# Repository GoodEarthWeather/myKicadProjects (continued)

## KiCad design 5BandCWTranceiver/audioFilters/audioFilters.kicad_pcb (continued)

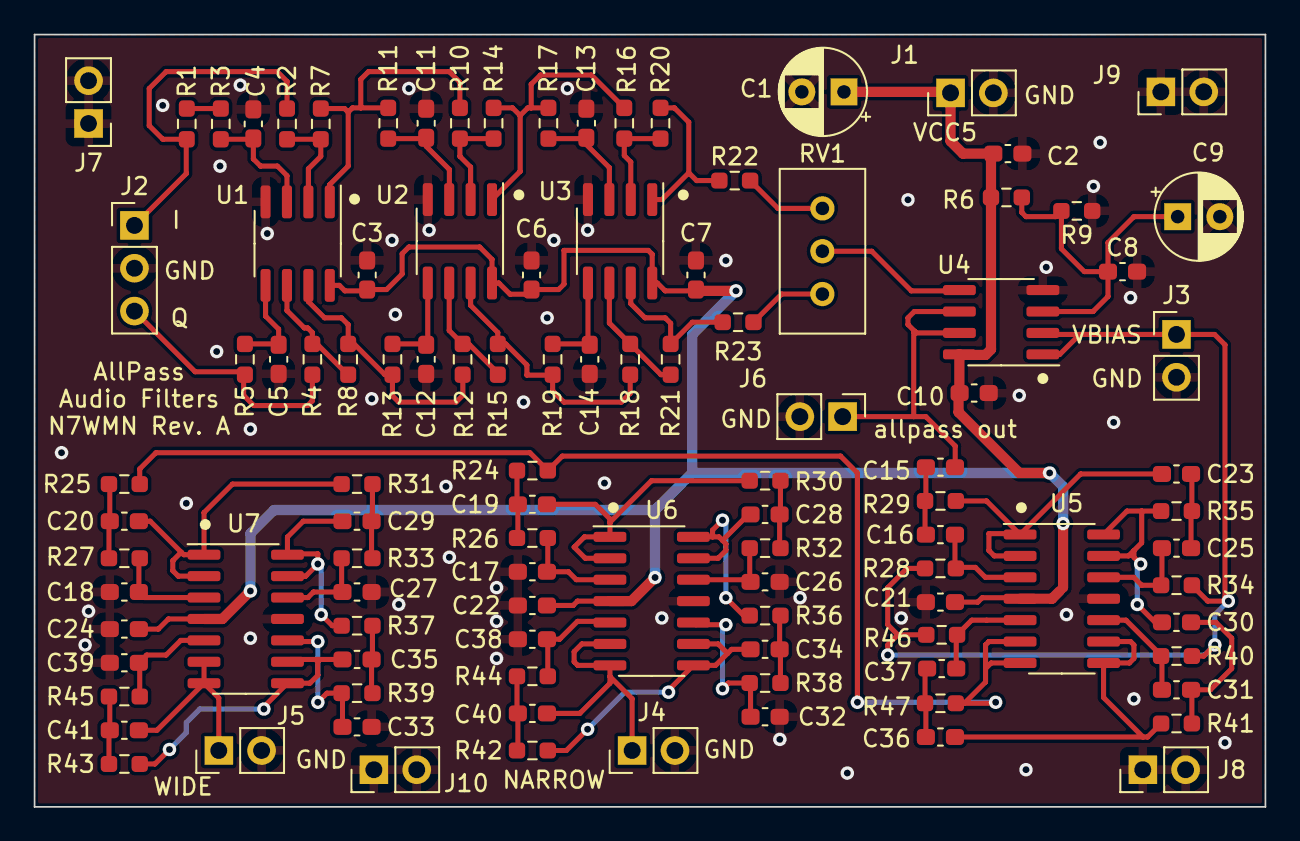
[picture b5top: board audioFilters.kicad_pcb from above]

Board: 2 copper layers, 73.0 x 45.8 mm, 106 parts (0 on the bottom side), 65 nets.

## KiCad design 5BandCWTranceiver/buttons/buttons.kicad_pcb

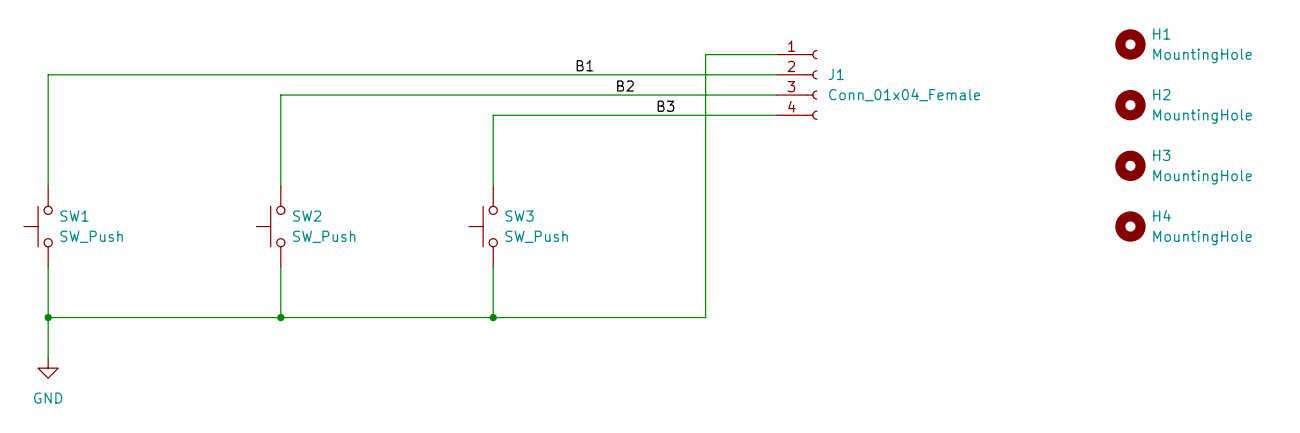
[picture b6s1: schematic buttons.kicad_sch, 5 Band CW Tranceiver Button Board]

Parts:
H1, H2, H3, H4: MountingHole; MountingHole_3.2mm_M3
J1: Conn_01x04_Female; PinHeader_1x04_P2.54mm_Vertical
SW1, SW2, SW3: SW_Push; SW_PUSH-12mm

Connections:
/B1: J1.2, SW1.2
/B2: J1.3, SW2.2
/B3: J1.4, SW3.2
GND: J1.1, SW1.1, SW2.1, SW3.1

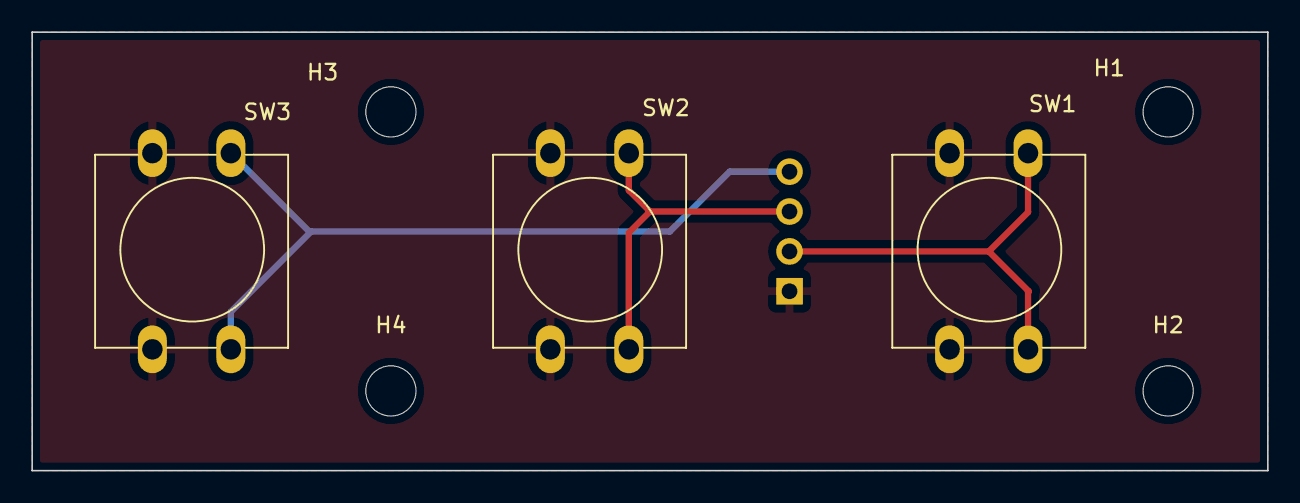
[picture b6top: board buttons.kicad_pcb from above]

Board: 2 copper layers, 78.7 x 27.9 mm, 8 parts (1 on the bottom side), 4 nets.

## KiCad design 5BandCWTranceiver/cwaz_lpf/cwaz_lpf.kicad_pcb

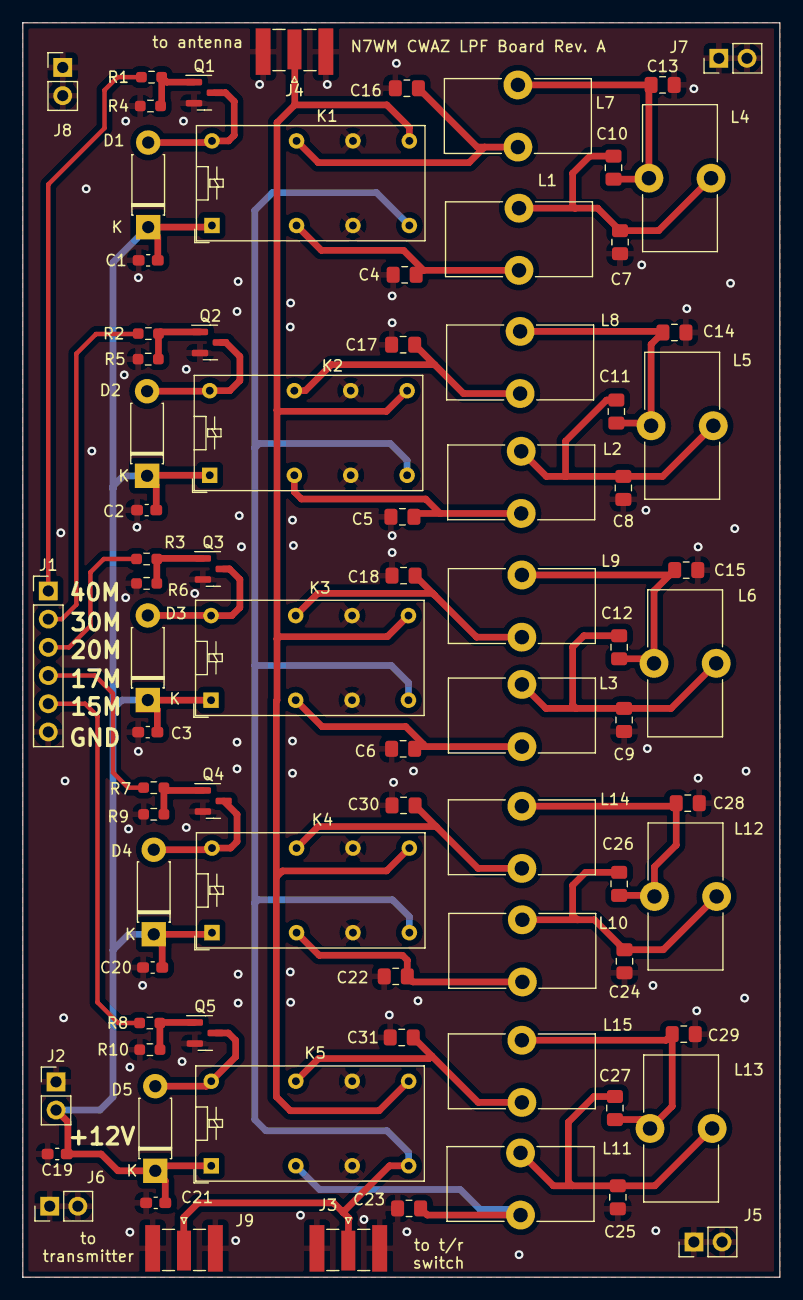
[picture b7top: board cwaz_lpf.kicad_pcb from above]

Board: 2 copper layers, 68.2 x 113.0 mm, 80 parts (0 on the bottom side), 39 nets.

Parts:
C1, C2, C3, C19, C20, C21: 0.1uF; C_0603_1608Metric_Pad1.08x0.95mm_HandSolder
C4, C16: 330p+100p; C_0805_2012Metric_Pad1.18x1.45mm_HandSolder
C5, C17: 150p+150p; C_0805_2012Metric_Pad1.18x1.45mm_HandSolder
C6, C18, C25, C29: 220p; C_0805_2012Metric_Pad1.18x1.45mm_HandSolder
C7, C13: 330p+330p; C_0805_2012Metric_Pad1.18x1.45mm_HandSolder
C8, C14: 470p; C_0805_2012Metric_Pad1.18x1.45mm_HandSolder
C9, C15: 330p; C_0805_2012Metric_Pad1.18x1.45mm_HandSolder
C10: 100p; C_0805_2012Metric_Pad1.18x1.45mm_HandSolder
C11: 68p; C_0805_2012Metric_Pad1.18x1.45mm_HandSolder
C12: 47p; C_0805_2012Metric_Pad1.18x1.45mm_HandSolder
C22, C30: 82p+82p; C_0805_2012Metric_Pad1.18x1.45mm_HandSolder
C23, C31: 150p; C_0805_2012Metric_Pad1.18x1.45mm_HandSolder
C24, C28: 100p+150p; C_0805_2012Metric_Pad1.18x1.45mm_HandSolder
C26: 39p; C_0805_2012Metric_Pad1.18x1.45mm_HandSolder
C27: 33p; C_0805_2012Metric_Pad1.18x1.45mm_HandSolder
D1, D2, D3, D4, D5: 1N4152; D_DO-41_SOD81_P7.62mm_Horizontal
J1: Conn_01x06_Male; PinHeader_1x06_P2.54mm_Vertical
J2, J5, J6, J7, J8: Conn_01x02_Male; PinHeader_1x02_P2.54mm_Vertical
J3, J4, J9: Conn_Coaxial; SMA_Samtec_SMA-J-P-X-ST-EM1_EdgeMount
K1, K2, K3, K4, K5: G5V-2; Relay_DPDT_Omron_G5V-2
L1, L7: 1.34uH; L_Toroid_Vertical_L13.0mm_W6.5mm_P5.60mm
L2, L8: 928nH; L_Toroid_Vertical_L13.0mm_W6.5mm_P5.60mm
L3, L9: 670nH; L_Toroid_Vertical_L13.0mm_W6.5mm_P5.60mm
L4: 1.22uH; L_Toroid_Vertical_L13.0mm_W6.5mm_P5.60mm
L5: 843nH; L_Toroid_Vertical_L13.0mm_W6.5mm_P5.60mm
L6: 608nH; L_Toroid_Vertical_L13.0mm_W6.5mm_P5.60mm
L10, L14: 519nH; L_Toroid_Vertical_L13.0mm_W6.5mm_P5.60mm
L11, L15: 447nH; L_Toroid_Vertical_L13.0mm_W6.5mm_P5.60mm
L12: 471nH; L_Toroid_Vertical_L13.0mm_W6.5mm_P5.60mm
L13: 406nH; L_Toroid_Vertical_L13.0mm_W6.5mm_P5.60mm
Q1, Q2, Q3, Q4, Q5: MMBT3904; SOT-23
R1, R2, R3, R4, R5, R6, R7, R8, R9, R10: R_US; R_0603_1608Metric_Pad0.98x0.95mm_HandSolder

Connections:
/15M: J1.5, R8.2
/17M: J1.4, R7.2
/20M: J1.3, R3.2
/30M: J1.2, R2.2
/40M: J1.1, R1.2
/VDD12: C1.1, C2.1, C3.1, C19.1, C20.1, C21.1, D1.1 (K), D2.1 (K), D3.1 (K), D4.1 (K), D5.1 (K), J2.2, K1.1, K2.1, K3.1, K4.1, K5.1
GND: C1.2, C2.2, C3.2, C4.2, C5.2, C6.2, C7.2, C8.2, C9.2, C13.2, C14.2, C15.2, C16.2, C17.2, C18.2, C19.2, C20.2, C21.2, C22.2, C23.2, C24.2, C25.2, C28.2, C29.2, C30.2, C31.2, J1.6, J2.1, J3.2 (Ext), J4.2 (Ext), J5.1, J5.2, J6.1, J6.2, J7.1, J7.2, J8.1, J8.2, J9.2 (Ext), K1.6, K1.11, K2.6, K2.11, K3.6, K3.11, K4.6, K4.11, K5.6, K5.11, Q1.2 (E), Q2.2 (E), Q3.2 (E), Q4.2 (E), Q5.2 (E), R4.2, R5.2, R6.2, R9.2, R10.2
unnamed: C5.1, K2.4, L2.2
unnamed: C6.1, K3.4, L3.2
unnamed: C10.1, C13.1, L4.1, L7.2
unnamed: C7.1, C10.2, L1.1, L4.2
unnamed: C11.1, C14.1, L5.1, L8.2
unnamed: C8.1, C11.2, L2.1, L5.2
unnamed: C12.1, C15.1, L6.1, L9.2
unnamed: C9.1, C12.2, L3.1, L6.2
unnamed: C16.1, K1.13, L7.1
unnamed: C17.1, K2.13, L8.1
unnamed: C18.1, K3.13, L9.1
unnamed: C23.1, K5.4, L11.2
unnamed: C24.1, C26.2, L10.1, L12.2
unnamed: C25.1, C27.2, L11.1, L13.2
unnamed: C26.1, C28.1, L12.1, L14.2
unnamed: C27.1, C29.1, L13.1, L15.2
unnamed: C30.1, K4.13, L14.1
unnamed: D1.2 (A), K1.16, Q1.3 (C)
unnamed: D2.2 (A), K2.16, Q2.3 (C)
unnamed: D3.2 (A), K3.16, Q3.3 (C)
unnamed: D4.2 (A), K4.16, Q4.3 (C)
unnamed: D5.2 (A), K5.16, Q5.3 (C)
unnamed: C4.1, K1.4, L1.2
unnamed: J3.1 (In), J9.1 (In), K1.8, K2.8, K3.8, K4.8, K5.8
unnamed: J4.1 (In), K1.9, K2.9, K3.9, K4.9, K5.9
unnamed: C22.1, K4.4, L10.2
unnamed: C31.1, K5.13, L15.1
unnamed: Q1.1 (B), R1.1, R4.1
unnamed: Q2.1 (B), R2.1, R5.1
unnamed: Q3.1 (B), R3.1, R6.1
unnamed: Q4.1 (B), R7.1, R9.1
unnamed: Q5.1 (B), R8.1, R10.1

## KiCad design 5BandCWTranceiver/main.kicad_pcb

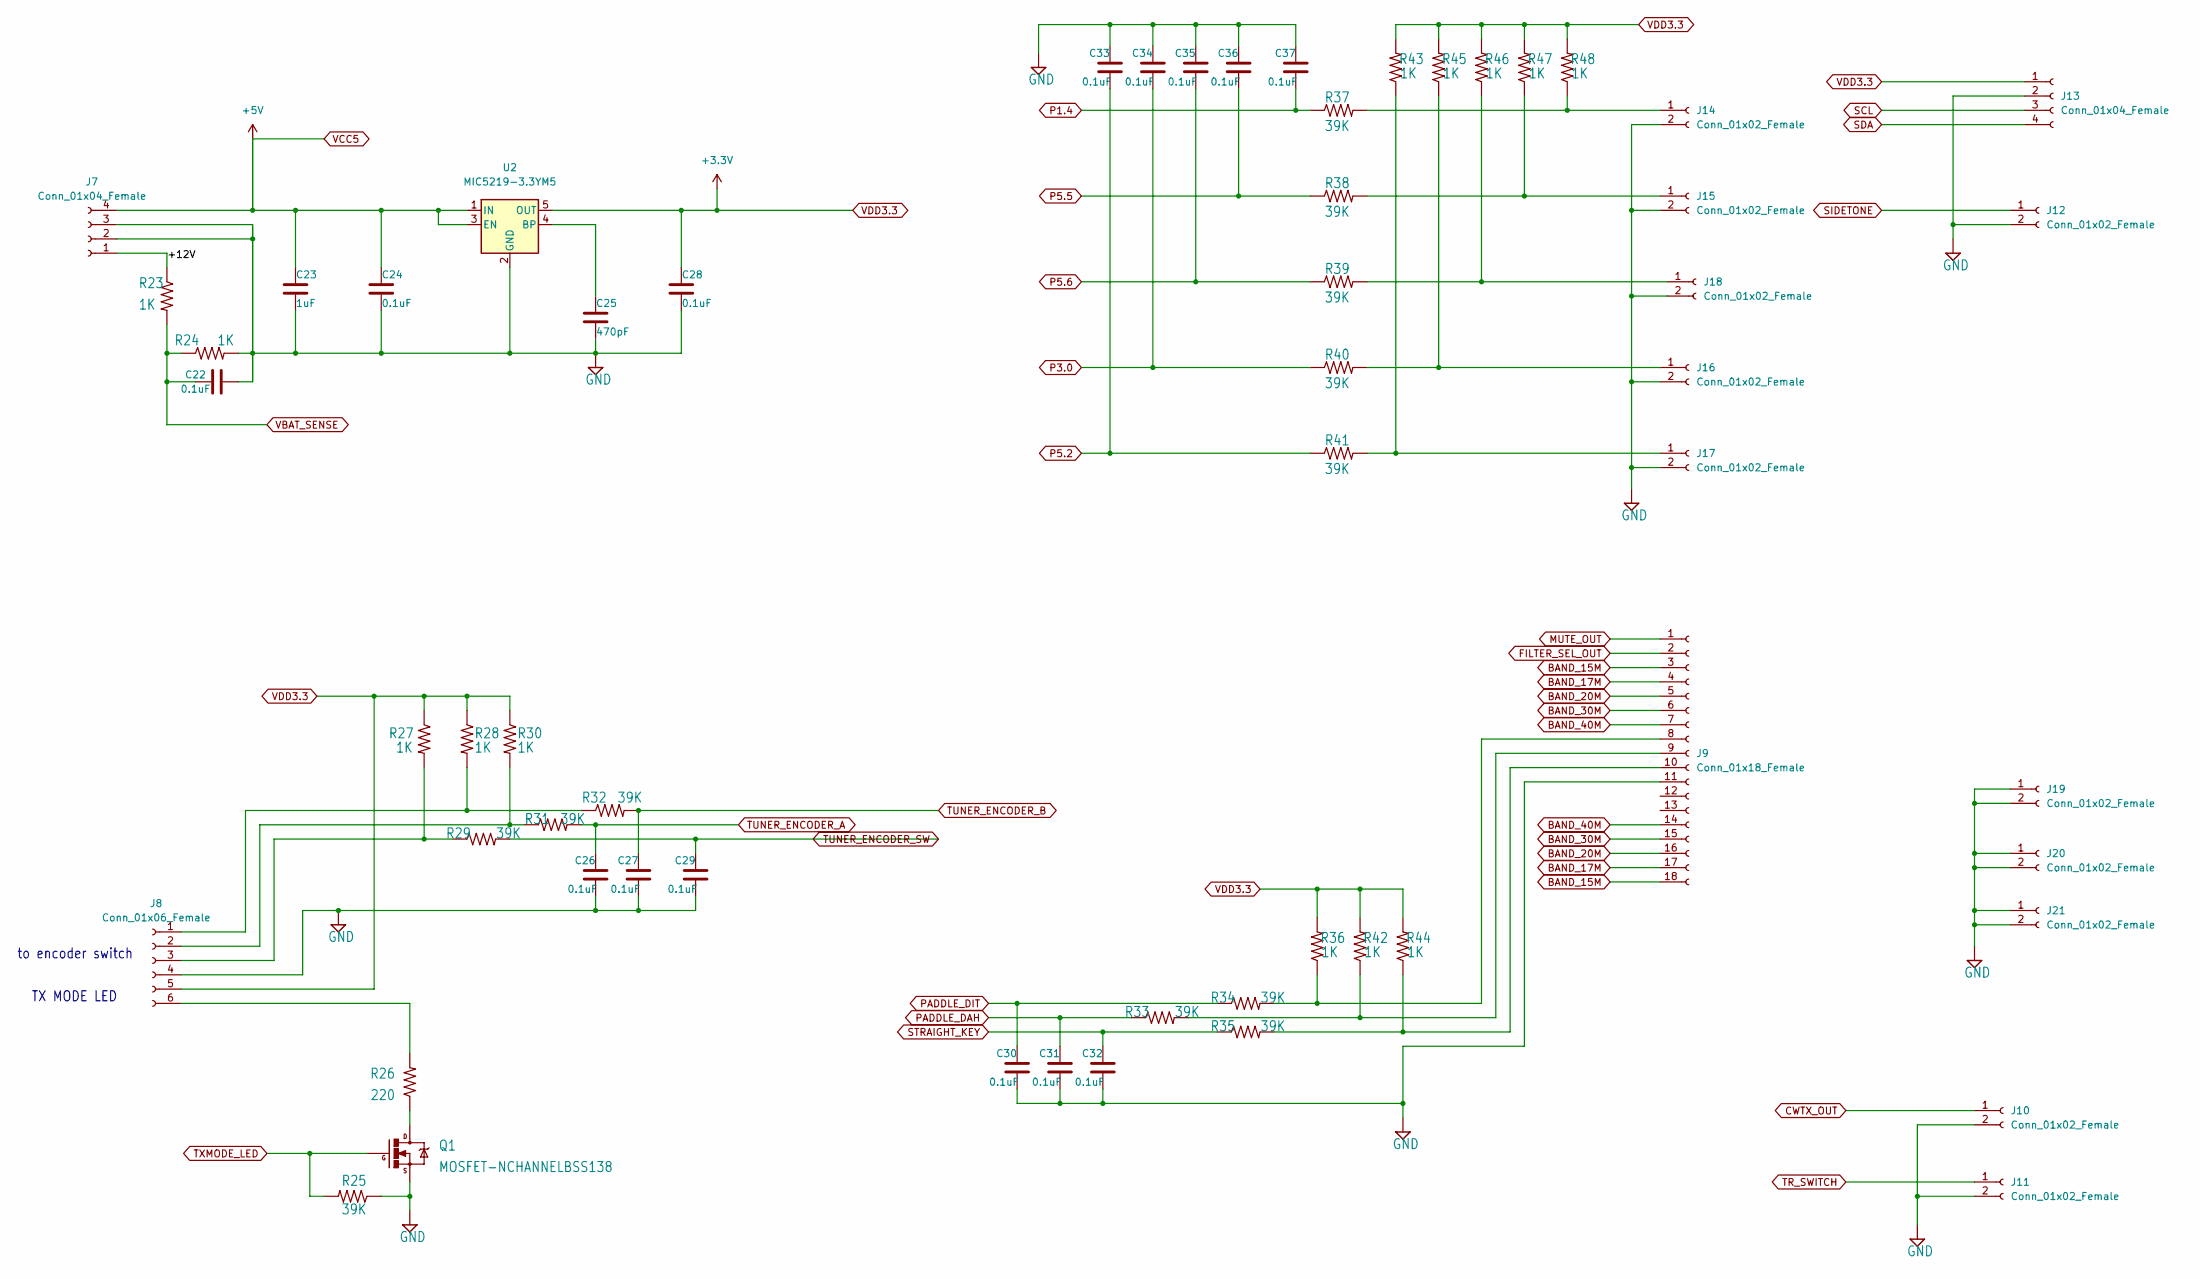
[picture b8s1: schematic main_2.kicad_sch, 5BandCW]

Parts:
C22, C24, C26, C27, C28, C29, C30, C31, C32, C33, C34, C35, C36, C37: 0.1uF; C_0603_1608Metric
C23: 1uF; C_0603_1608Metric
C25: 470pF; C_0603_1608Metric
J7, J13: Conn_01x04_Female; PinHeader_1x04_P2.54mm_Vertical
J8: Conn_01x06_Female; PinHeader_1x06_P2.54mm_Vertical
J9: Conn_01x18_Female; PinHeader_1x18_P2.54mm_Vertical
J10, J11, J12, J14, J15, J16, J17, J18, J19, J20, J21: Conn_01x02_Female; PinHeader_1x02_P2.54mm_Vertical
Q1: MOSFET-NCHANNELBSS138; SOT-23
R23, R24, R27, R28, R30, R36, R42, R43, R44, R45, R46, R47, R48: 1K; R_0603_1608Metric
R25, R29, R31, R32, R33, R34, R35, R37, R38, R39, R40, R41: 39K; R_0603_1608Metric
R26: 220; R_0603_1608Metric
U2: MIC5219-3.3YM5; SOT-23-5

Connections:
/main_2/+12V: J7.1, R23.1
BAND_15M: J9.3, J9.18; also elsewhere on the board
BAND_17M: J9.4, J9.17; also elsewhere on the board
BAND_20M: J9.5, J9.16; also elsewhere on the board
BAND_30M: J9.6, J9.15; also elsewhere on the board
BAND_40M: J9.7, J9.14; also elsewhere on the board
CWTX_OUT: J10.1; also elsewhere on the board
FILTER_SEL_OUT: J9.2; also elsewhere on the board
GND: C22.2, C23.2, C24.2, C25.2, C26.2, C27.2, C28.2, C29.2, C30.2, C31.2, C32.2, C33.1, C34.1, C35.1, C36.1, C37.1, J7.2, J7.3, J8.4, J9.11, J10.2, J11.2, J12.2, J13.2, J14.2, J15.2, J16.2, J17.2, J18.2, J19.1, J19.2, J20.1, J20.2, J21.1, J21.2, Q1.2 (S), R24.2, R25.1, U2.2 (GND); also elsewhere on the board
MUTE_OUT: J9.1; also elsewhere on the board
unnamed: C25.1, U2.4 (BP)
unnamed: J8.1, R28.2, R32.1
unnamed: J8.2, R30.2, R31.1
unnamed: J8.3, R27.2, R29.1
unnamed: J8.6, R26.2
unnamed: J9.8, R34.2, R36.1
unnamed: J9.9, R33.2, R42.1
unnamed: J9.10, R35.2, R44.1
unnamed: J14.1, R37.2, R48.1
unnamed: J15.1, R38.2, R47.1
unnamed: J16.1, R40.2, R45.1
unnamed: J17.1, R41.2, R43.1
unnamed: J18.1, R39.2, R46.1
unnamed: Q1.3 (D), R26.1
P1.4: C37.2, R37.1; also elsewhere on the board
P3.0: C34.2, R40.1; also elsewhere on the board
P5.2: C33.2, R41.1; also elsewhere on the board
P5.5: C36.2, R38.1; also elsewhere on the board
P5.6: C35.2, R39.1; also elsewhere on the board
PADDLE_DAH: C31.1, R33.1; also elsewhere on the board
PADDLE_DIT: C30.1, R34.1; also elsewhere on the board
SCL: J13.3; also elsewhere on the board
SDA: J13.4; also elsewhere on the board
SIDETONE: J12.1; also elsewhere on the board
STRAIGHT_KEY: C32.1, R35.1; also elsewhere on the board
TR_SWITCH: J11.1; also elsewhere on the board
TUNER_ENCODER_A: C26.1, R31.2; also elsewhere on the board
TUNER_ENCODER_B: C27.1, R32.2; also elsewhere on the board
TUNER_ENCODER_SW: C29.1, R29.2; also elsewhere on the board
TXMODE_LED: Q1.1 (G), R25.2; also elsewhere on the board
VBAT_SENSE: C22.1, R23.2, R24.1; also elsewhere on the board
VCC5: C23.1, C24.1, J7.4, U2.1 (IN), U2.3 (EN); also elsewhere on the board
VDD3.3: C28.1, J8.5, J13.1, R27.1, R28.1, R30.1, R36.2, R42.2, R43.2, R44.2, R45.2, R46.2, R47.2, R48.2, U2.5 (OUT); also elsewhere on the board

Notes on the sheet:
to encoder switch
TX MODE LED

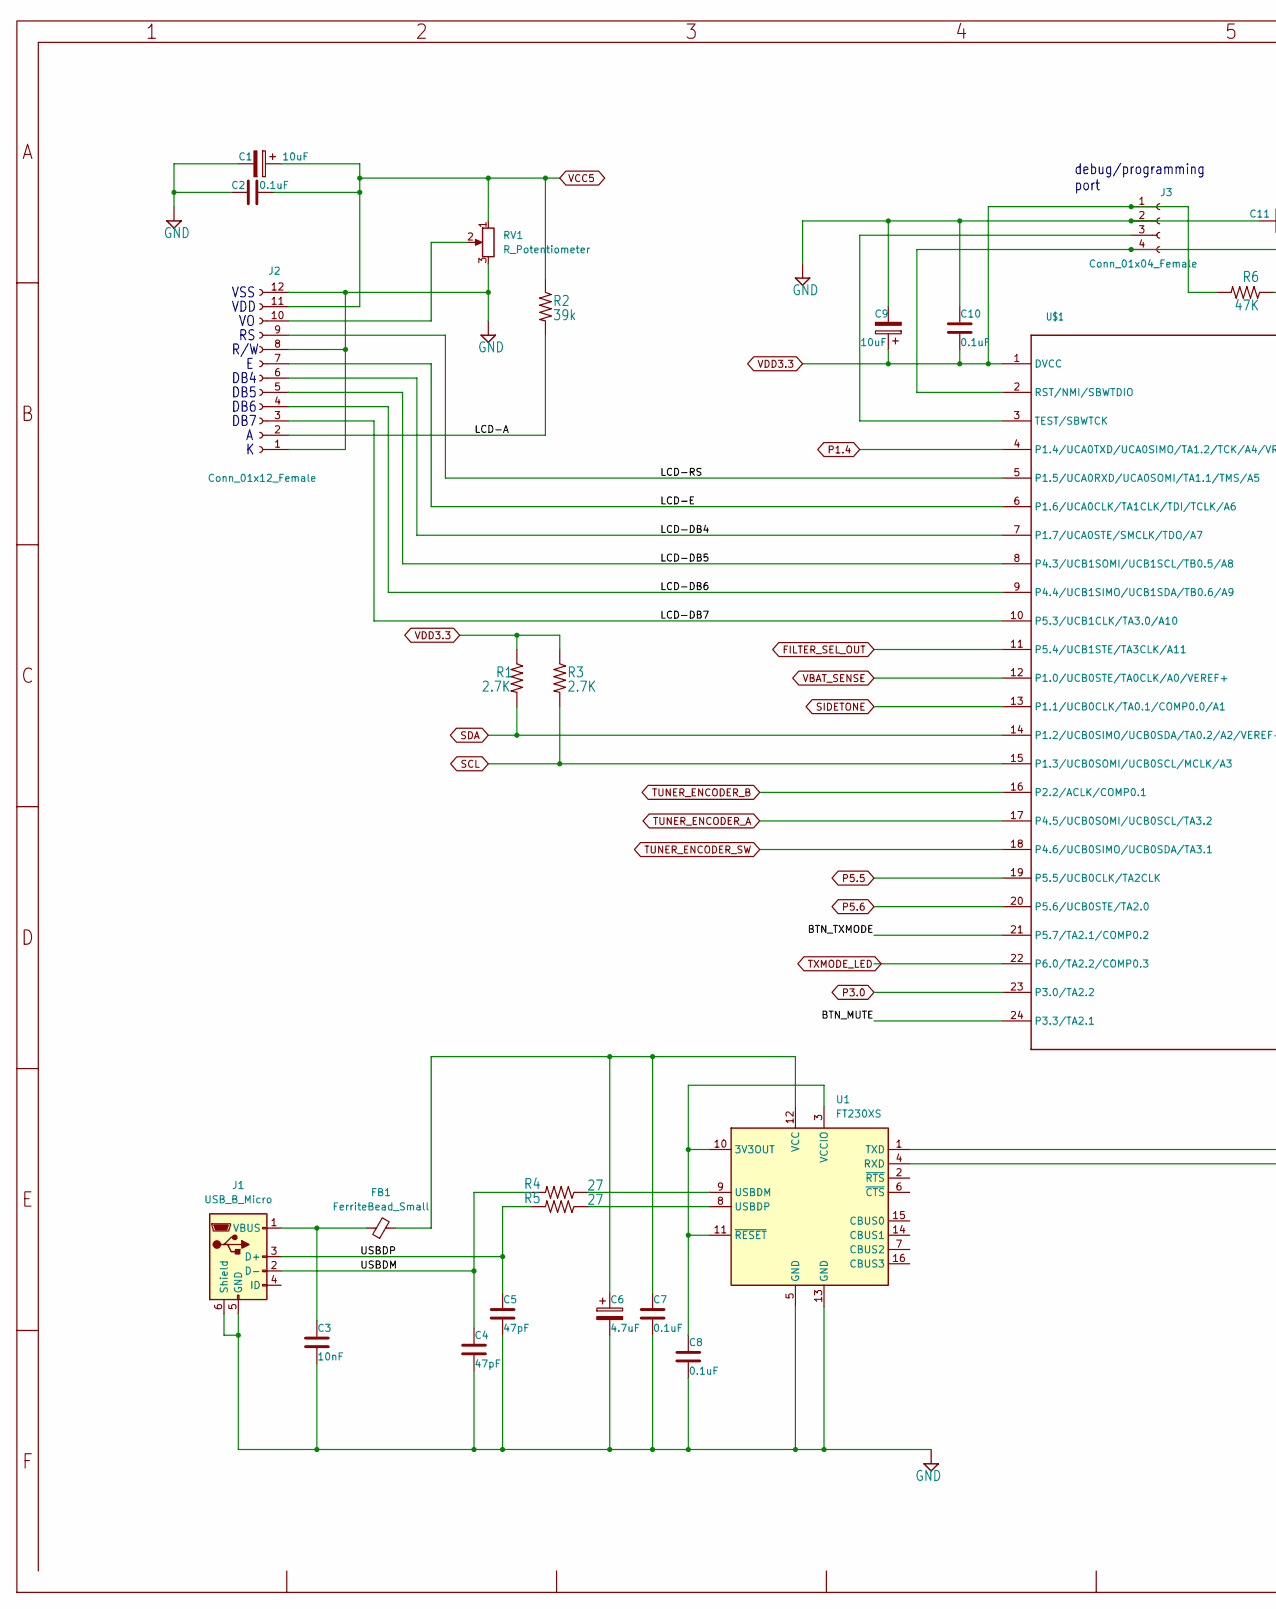
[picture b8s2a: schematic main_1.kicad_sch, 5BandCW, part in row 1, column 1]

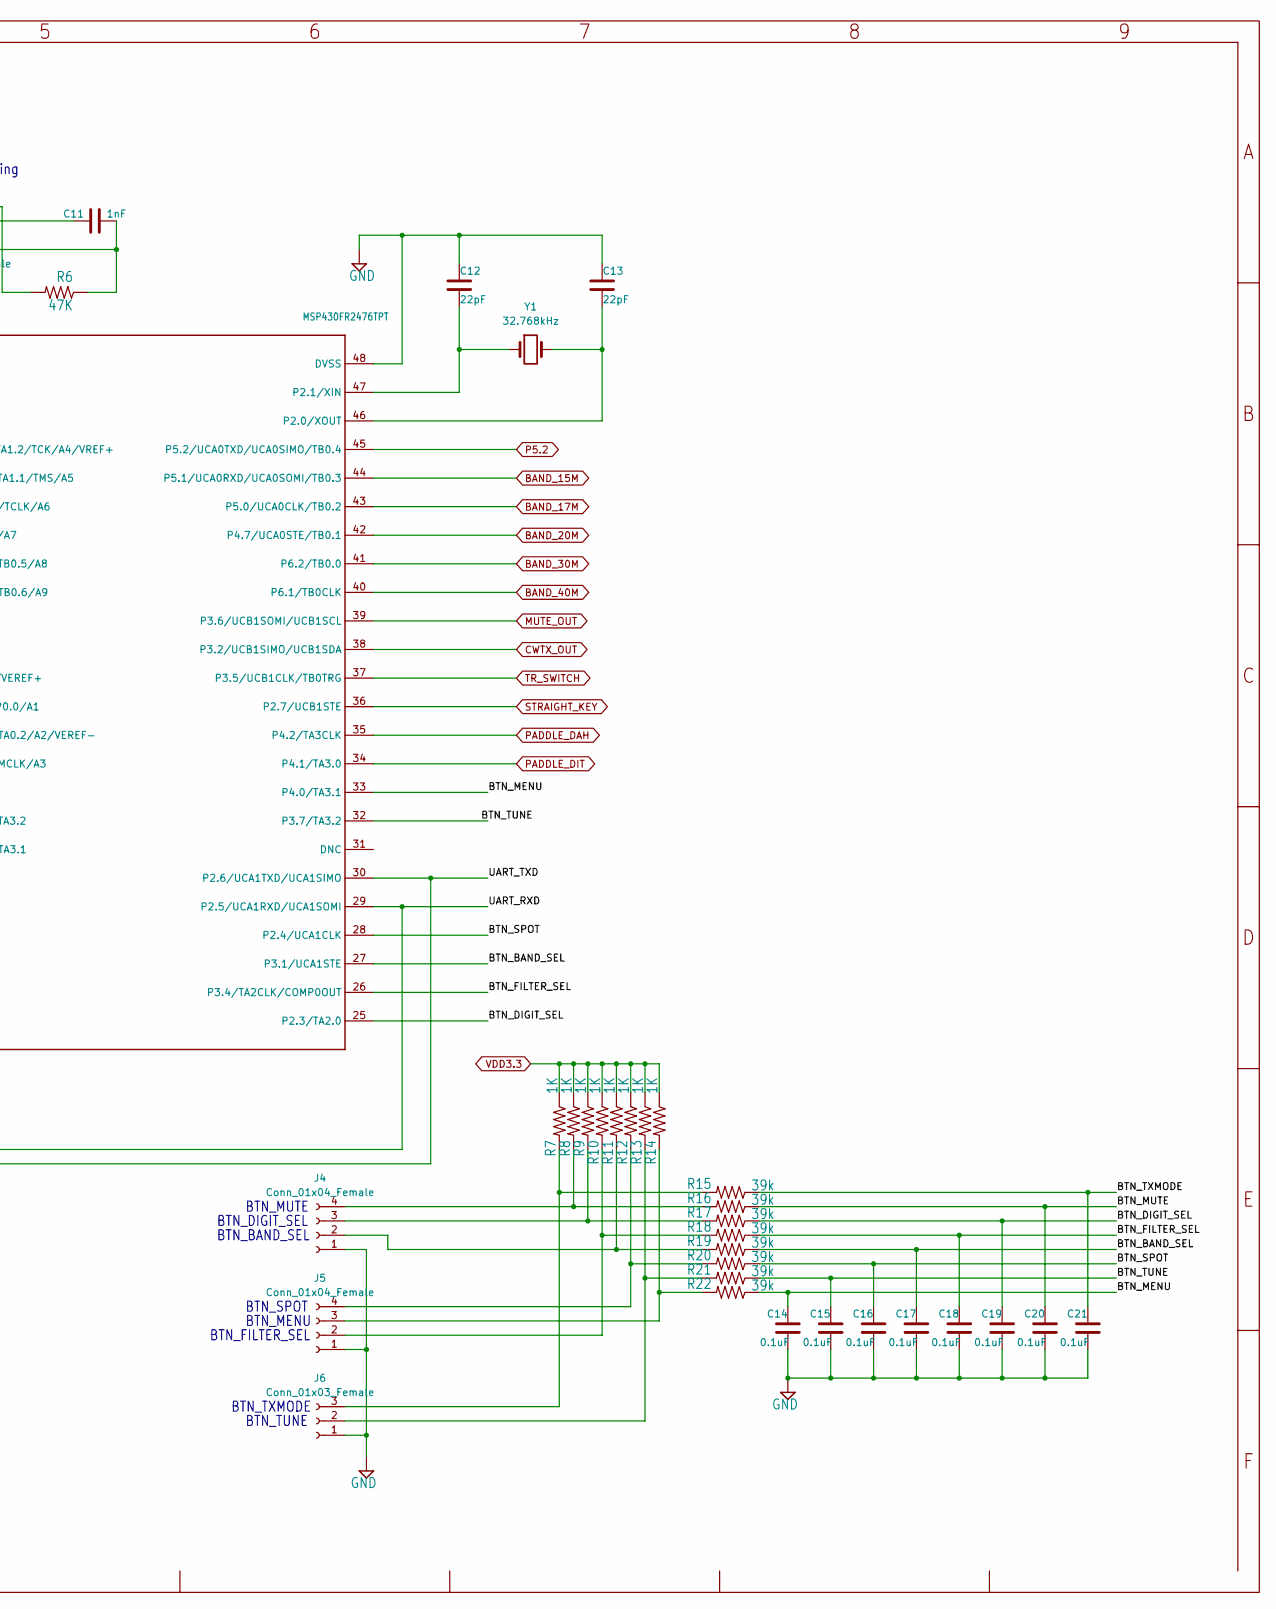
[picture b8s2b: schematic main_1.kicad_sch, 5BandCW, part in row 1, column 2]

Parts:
C1, C9: 10uF; CP_Radial_D5.0mm_P2.00mm
C2, C7, C8, C10, C14, C15, C16, C17, C18, C19, C20, C21: 0.1uF; C_0603_1608Metric
C3: 10nF; C_0603_1608Metric
C4, C5: 47pF; C_0603_1608Metric
C6: 4.7uF; CP_Radial_D5.0mm_P2.00mm
C11: 1nF; C_0603_1608Metric
C12, C13: 22pF; C_0603_1608Metric
FB1: FerriteBead_Small; R_0603_1608Metric
J1: USB_B_Micro; USB_Micro-B_Molex-105017-0001
J2: Conn_01x12_Female; PinHeader_1x12_P2.54mm_Vertical
J3, J4, J5: Conn_01x04_Female; PinHeader_1x04_P2.54mm_Vertical
J6: Conn_01x03_Female; PinHeader_1x03_P2.54mm_Vertical
R1, R3: 2.7K; R_0603_1608Metric
R2, R15, R16, R17, R18, R19, R20, R21, R22: 39k; R_0603_1608Metric
R4, R5: 27; R_0603_1608Metric
R6: 47K; R_0603_1608Metric
R7, R8, R9, R10, R11, R12, R13, R14: 1K; R_0603_1608Metric
RV1: R_Potentiometer; Potentiometer_Bourns_3386C_Horizontal
U1: FT230XS; SSOP-16_3.9x4.9mm_P0.635mm
U$1: MSP430FR2476TPT; LQFP-48_7x7mm_P0.5mm
Y1: 32.768kHz; Crystal_SMD_2012-2Pin_2.0x1.2mm

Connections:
/main_1/BTN_BAND_SEL: C17.1, R19.1, U$1.27 (P3.1/UCA1STE)
/main_1/BTN_DIGIT_SEL: C19.1, R17.1, U$1.25 (P2.3/TA2.0)
/main_1/BTN_FILTER_SEL: C18.1, R18.1, U$1.26 (P3.4/TA2CLK/COMP0OUT)
/main_1/BTN_MENU: C14.1, R22.1, U$1.33 (P4.0/TA3.1)
/main_1/BTN_MUTE: C20.1, R16.1, U$1.24 (P3.3/TA2.1)
/main_1/BTN_SPOT: C16.1, R20.1, U$1.28 (P2.4/UCA1CLK)
/main_1/BTN_TUNE: C15.1, R21.1, U$1.32 (P3.7/TA3.2)
/main_1/BTN_TXMODE: C21.1, R15.1, U$1.21 (P5.7/TA2.1/COMP0.2)
/main_1/LCD-A: J2.2, R2.2
/main_1/LCD-DB4: J2.6, U$1.7 (P1.7/UCA0STE/SMCLK/TDO/A7)
/main_1/LCD-DB5: J2.5, U$1.8 (P4.3/UCB1SOMI/UCB1SCL/TB0.5/A8)
/main_1/LCD-DB6: J2.4, U$1.9 (P4.4/UCB1SIMO/UCB1SDA/TB0.6/A9)
/main_1/LCD-DB7: J2.3, U$1.10 (P5.3/UCB1CLK/TA3.0/A10)
/main_1/LCD-E: J2.7, U$1.6 (P1.6/UCA0CLK/TA1CLK/TDI/TCLK/A6)
/main_1/LCD-RS: J2.9, U$1.5 (P1.5/UCA0RXD/UCA0SOMI/TA1.1/TMS/A5)
/main_1/UART_RXD: U1.1 (TXD), U$1.29 (P2.5/UCA1RXD/UCA1SOMI)
/main_1/UART_TXD: U1.4 (RXD), U$1.30 (P2.6/UCA1TXD/UCA1SIMO)
/main_1/USBDM: C4.1, J1.2 (D-), R4.2
/main_1/USBDP: C5.1, J1.3 (D+), R5.2
BAND_15M: U$1.44 (P5.1/UCA0RXD/UCA0SOMI/TB0.3); also elsewhere on the board
BAND_17M: U$1.43 (P5.0/UCA0CLK/TB0.2); also elsewhere on the board
BAND_20M: U$1.42 (P4.7/UCA0STE/TB0.1); also elsewhere on the board
BAND_30M: U$1.41 (P6.2/TB0.0); also elsewhere on the board
BAND_40M: U$1.40 (P6.1/TB0CLK); also elsewhere on the board
CWTX_OUT: U$1.38 (P3.2/UCB1SIMO/UCB1SDA); also elsewhere on the board
FILTER_SEL_OUT: U$1.11 (P5.4/UCB1STE/TA3CLK/A11); also elsewhere on the board
GND: C1.2, C2.1, C3.2, C4.2, C5.2, C6.2, C7.2, C8.2, C9.2, C10.1, C11.1, C12.1, C13.1, C14.2, C15.2, C16.2, C17.2, C18.2, C19.2, C20.2, C21.2, J1.5 (GND), J1.6 (Shield), J2.1, J2.8, J2.12, J3.2, J4.1, J5.1, J6.1, RV1.3, U1.5 (GND), U1.13 (GND), U$1.48 (DVSS); also elsewhere on the board
MUTE_OUT: U$1.39 (P3.6/UCB1SOMI/UCB1SCL); also elsewhere on the board
unnamed: C3.1, FB1.1, J1.1 (VBUS)
unnamed: C6.1, C7.1, FB1.2, U1.12 (VCC)
unnamed: C8.1, U1.3 (VCCIO), U1.10 (3V3OUT), U1.11 (~RESET)
unnamed: C11.2, J3.4, R6.1, U$1.2 (RST/NMI/SBWTDIO)
unnamed: C12.2, U$1.47 (P2.1/XIN), Y1.1
unnamed: C13.2, U$1.46 (P2.0/XOUT), Y1.2
unnamed: J2.10, RV1.2
unnamed: J3.3, U$1.3 (TEST/SBWTCK)
unnamed: J4.2, R11.2, R19.2
unnamed: J4.3, R9.2, R17.2
unnamed: J4.4, R8.2, R16.2
unnamed: J5.2, R10.2, R18.2
unnamed: J5.3, R14.2, R22.2
unnamed: J5.4, R12.2, R20.2
unnamed: J6.2, R13.2, R21.2
unnamed: J6.3, R7.2, R15.2
unnamed: R4.1, U1.9 (USBDM)
unnamed: R5.1, U1.8 (USBDP)
P1.4: U$1.4 (P1.4/UCA0TXD/UCA0SIMO/TA1.2/TCK/A4/VREF+); also elsewhere on the board
P3.0: U$1.23 (P3.0/TA2.2); also elsewhere on the board
P5.2: U$1.45 (P5.2/UCA0TXD/UCA0SIMO/TB0.4); also elsewhere on the board
P5.5: U$1.19 (P5.5/UCB0CLK/TA2CLK); also elsewhere on the board
P5.6: U$1.20 (P5.6/UCB0STE/TA2.0); also elsewhere on the board
PADDLE_DAH: U$1.35 (P4.2/TA3CLK); also elsewhere on the board
PADDLE_DIT: U$1.34 (P4.1/TA3.0); also elsewhere on the board
SCL: R3.2, U$1.15 (P1.3/UCB0SOMI/UCB0SCL/MCLK/A3); also elsewhere on the board
SDA: R1.2, U$1.14 (P1.2/UCB0SIMO/UCB0SDA/TA0.2/A2/VEREF-); also elsewhere on the board
SIDETONE: U$1.13 (P1.1/UCB0CLK/TA0.1/COMP0.0/A1); also elsewhere on the board
STRAIGHT_KEY: U$1.36 (P2.7/UCB1STE); also elsewhere on the board
TR_SWITCH: U$1.37 (P3.5/UCB1CLK/TB0TRG); also elsewhere on the board
TUNER_ENCODER_A: U$1.17 (P4.5/UCB0SOMI/UCB0SCL/TA3.2); also elsewhere on the board
TUNER_ENCODER_B: U$1.16 (P2.2/ACLK/COMP0.1); also elsewhere on the board
TUNER_ENCODER_SW: U$1.18 (P4.6/UCB0SIMO/UCB0SDA/TA3.1); also elsewhere on the board
TXMODE_LED: U$1.22 (P6.0/TA2.2/COMP0.3); also elsewhere on the board
VBAT_SENSE: U$1.12 (P1.0/UCB0STE/TA0CLK/A0/VEREF+); also elsewhere on the board
VCC5: C1.1, C2.2, J2.11, R2.1, RV1.1; also elsewhere on the board
VDD3.3: C9.1, C10.2, J3.1, R1.1, R3.1, R6.2, R7.1, R8.1, R9.1, R10.1, R11.1, R12.1, R13.1, R14.1, U$1.1 (DVCC); also elsewhere on the board

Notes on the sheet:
BTN_FILTER_SEL
VDD
VSS
DB5
BTN_BAND_SEL
BTN_MUTE
BTN_TUNE
DB4
BTN_DIGIT_SEL
DB6
BTN_TXMODE
R/W
DB7
debug/programming port
BTN_MENU
BTN_SPOT

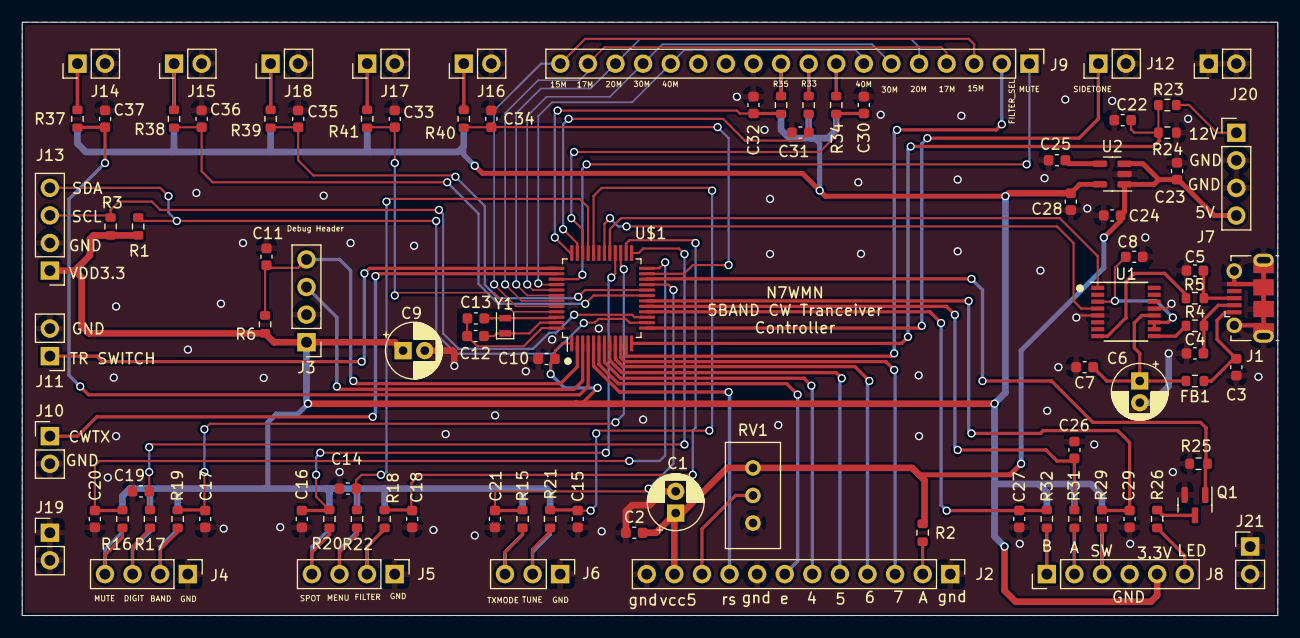
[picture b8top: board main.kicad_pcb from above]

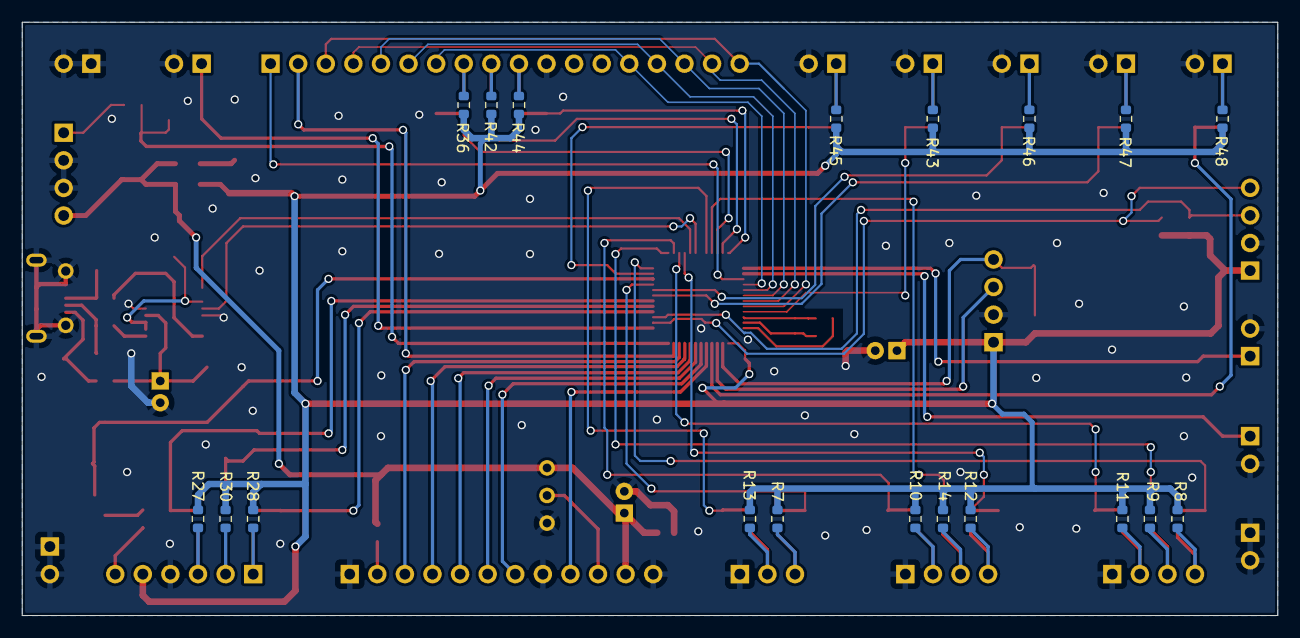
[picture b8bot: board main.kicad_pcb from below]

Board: 2 copper layers, 115.6 x 54.6 mm, 113 parts (19 on the bottom side), 80 nets.
